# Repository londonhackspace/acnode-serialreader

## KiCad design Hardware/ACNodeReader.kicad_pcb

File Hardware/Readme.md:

ACNode Serial Reader Hardware
=============

Errata - V1.1
----
* The RX and TX lines are backwards on connector J6 - Silkscreen is as intended NOT as implemented!

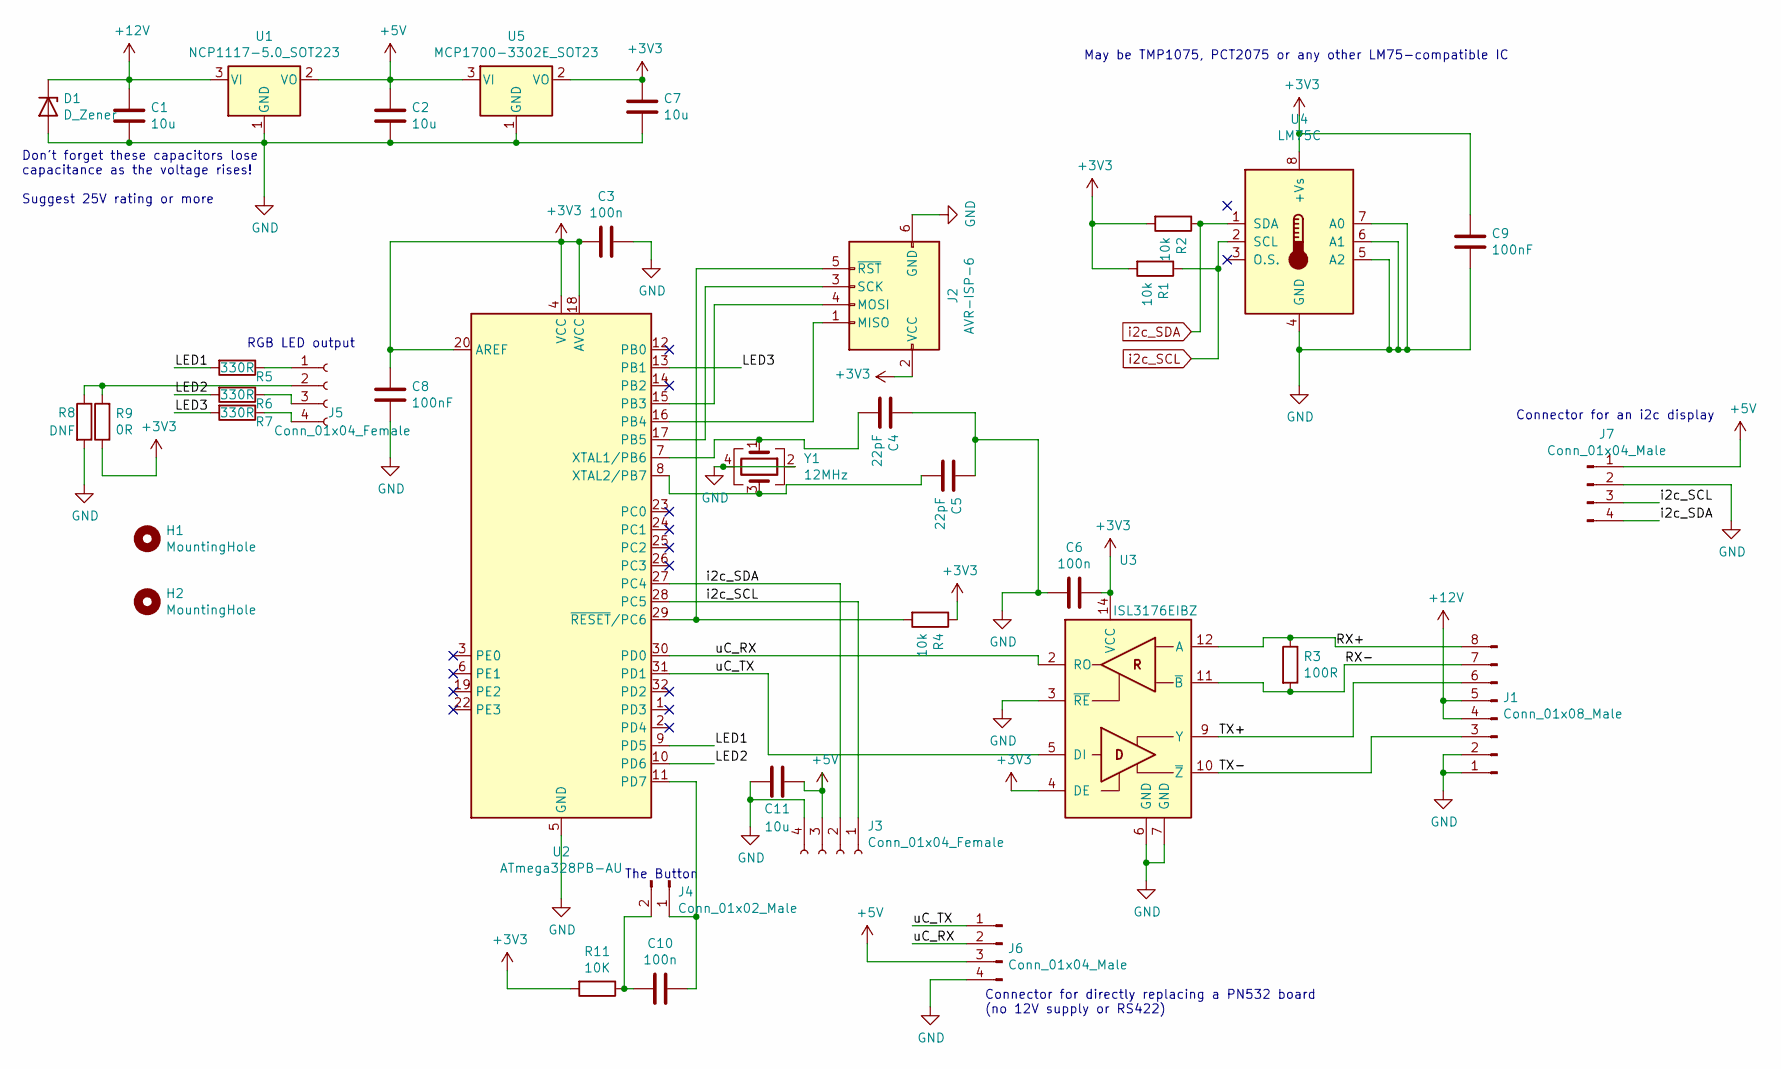
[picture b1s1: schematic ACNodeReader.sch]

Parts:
C1, C2, C7, C11: 10u; C_0805_2012Metric
C3, C6, C10: 100n; C_0603_1608Metric
C4, C5: 22pF; C_0603_1608Metric
C8, C9: 100nF; C_0603_1608Metric
D1: D_Zener; D_SOD-323F
H1, H2: MountingHole; MountingHole_3.2mm_M3_DIN965
J1: Conn_01x08_Male; PinHeader_1x08_P2.54mm_Horizontal
J2: AVR-ISP-6; TC2030-MCP-NL
J3: Conn_01x04_Female; PinHeader_1x04_P2.54mm_Vertical
J4: Conn_01x02_Male; PinHeader_1x02_P2.54mm_Horizontal
J5: Conn_01x04_Female; PinHeader_1x04_P2.54mm_Horizontal
J6: Conn_01x04_Male; PinHeader_1x04_P2.54mm_Horizontal
J7: Conn_01x04_Male; PinHeader_1x04_P2.54mm_Vertical
R1, R2, R4: 10k; R_0603_1608Metric
R3: 100R; R_0603_1608Metric
R5, R6, R7: 330R; R_0603_1608Metric
R8: DNF; R_0603_1608Metric
R9: 0R; R_0603_1608Metric
R11: 10K; R_0603_1608Metric
U1: NCP1117-5.0_SOT223; SOT-223-3_TabPin2
U2: ATmega328PB-AU; TQFP-32_7x7mm_P0.8mm
U3: ISL3176EIBZ; SOIC-14_3.9x8.7mm_P1.27mm
U4: LM75C; SO-8_3.9x4.9mm_P1.27mm
U5: MCP1700-3302E_SOT23; SOT-23
Y1: 12MHz; Crystal_SMD_7050-4Pin_7.0x5.0mm

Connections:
+3V3: C3.2, C6.1, C7.1, C8.1, C9.1, J2.2 (VCC), R1.2, R2.2, R4.1, R9.1, R11.2, U2.4 (VCC), U2.18 (AVCC), U2.20 (AREF), U3.4 (DE), U3.14 (VCC), U4.8 (+Vs), U5.2 (VO)
+5V: C2.1, C11.1, J3.3, J6.3, J7.1, U1.2 (VO), U5.3 (VI)
+12V: C1.1, D1.1 (K), J1.4, J1.5, U1.3 (VI)
/LED1: R5.2, U2.9 (PD5)
/LED2: R6.2, U2.10 (PD6)
/LED3: R7.2, U2.13 (PB1)
/RX+: J1.8, R3.1, U3.12 (A)
/RX-: J1.7, R3.2, U3.11 (~B)
/TX+: J1.6, U3.9 (Y)
/TX-: J1.3, U3.10 (~Z~)
/uC_RX: J6.2, U2.30 (PD0), U3.2 (RO)
/uC_TX: J6.1, U2.31 (PD1), U3.5 (DI)
GND: C1.2, C2.2, C3.1, C4.1, C5.1, C6.2, C7.2, C8.2, C9.2, C11.2, D1.2 (A), J1.1, J1.2, J2.6 (GND), J3.4, J6.4, J7.2, R8.2, U1.1 (GND), U2.5 (GND), U2.21 (GND), U3.3 (~RE), U3.6 (GND), U3.7 (GND), U4.4 (GND), U4.5 (A2), U4.6 (A1), U4.7 (A0), U5.1 (GND), Y1.2, Y1.4
unnamed: C4.2, U2.7 (XTAL1/PB6), Y1.1
unnamed: C5.2, U2.8 (XTAL2/PB7), Y1.3
unnamed: C10.1, J4.1, U2.11 (PD7)
unnamed: C10.2, J4.2, R11.1
unnamed: J2.1 (MISO), U2.16 (PB4)
unnamed: J2.3 (SCK), U2.17 (PB5)
unnamed: J2.4 (MOSI), U2.15 (PB3)
unnamed: J2.5 (~RST), R4.2, U2.29 (~RESET~/PC6)
unnamed: J5.1, R5.1
unnamed: J5.2, R8.1, R9.2
unnamed: J5.3, R6.1
unnamed: J5.4, R7.1
i2c_SCL: J3.1, J7.3, R1.1, U2.28 (PC5), U4.2 (SCL)
i2c_SDA: J3.2, J7.4, R2.1, U2.27 (PC4), U4.1 (SDA)

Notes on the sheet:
May be TMP1075, PCT2075 or any other LM75-compatible IC
Connector for an i2c display
Connector for directly replacing a PN532 board (no 12V supply or RS422)
The Button
RGB LED output
Don't forget these capacitors lose capacitance as the voltage rises! Suggest 25V rating or more

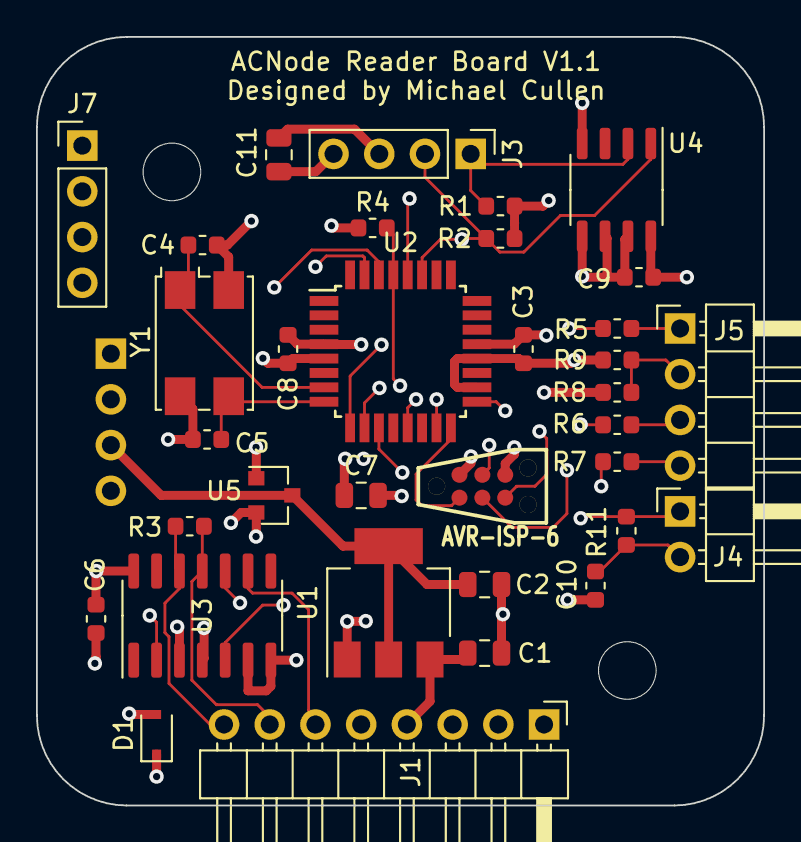
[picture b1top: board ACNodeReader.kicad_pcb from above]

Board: 4 copper layers, 40.4 x 42.7 mm, 37 parts (1 on the bottom side), 27 nets.

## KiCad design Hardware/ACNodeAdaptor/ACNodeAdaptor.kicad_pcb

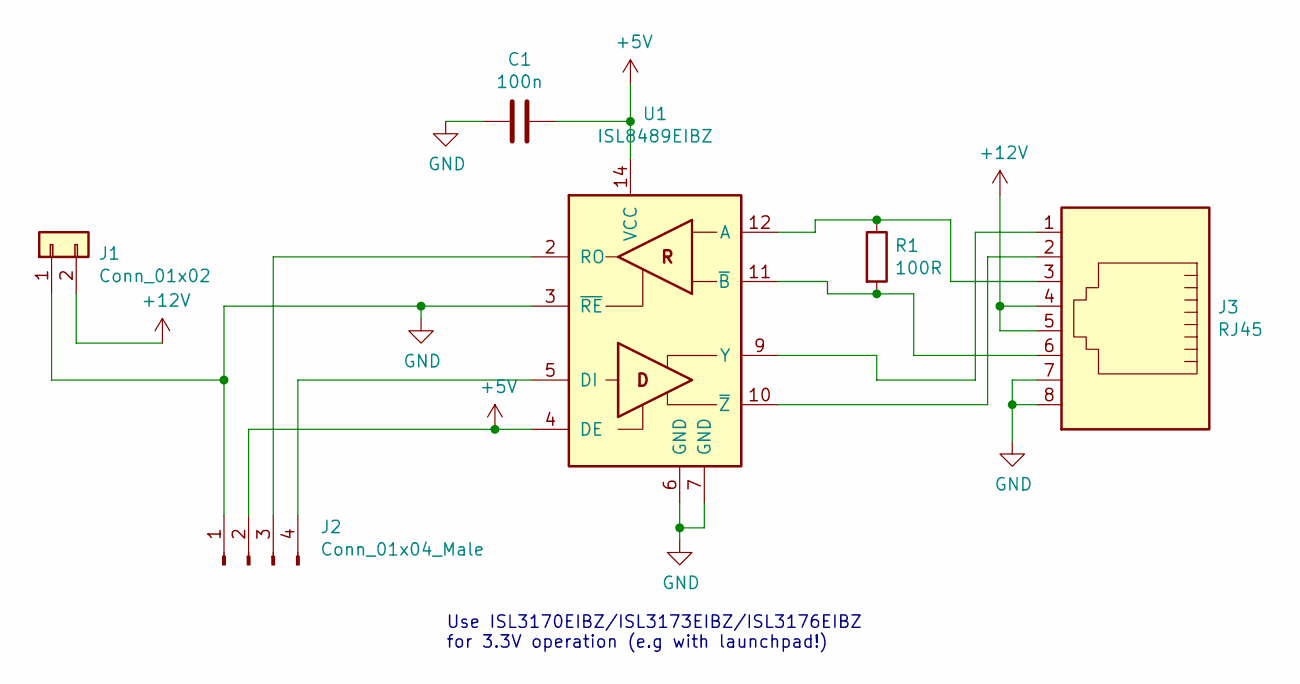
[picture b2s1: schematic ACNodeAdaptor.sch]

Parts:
C1: 100n; C_0603_1608Metric
J1: Conn_01x02; Connector-5.08mm
J2: Conn_01x04_Male; PinHeader_1x04_P2.54mm_Vertical
J3: RJ45; RJ45_Amphenol_54602-x08_Horizontal
R1: 100R; R_0603_1608Metric
U1: ISL8489EIBZ; SOIC-14_3.9x8.7mm_P1.27mm

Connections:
+5V: C1.1, J2.2, U1.4 (DE), U1.14 (VCC)
+12V: J1.2, J3.4, J3.5
GND: C1.2, J1.1, J2.1, J3.7, J3.8, U1.3 (~RE), U1.6 (GND), U1.7 (GND)
unnamed: J2.3, U1.2 (RO)
unnamed: J2.4, U1.5 (DI)
unnamed: J3.1, U1.9 (Y)
unnamed: J3.2, U1.10 (~Z~)
unnamed: J3.3, R1.1, U1.12 (A)
unnamed: J3.6, R1.2, U1.11 (~B)

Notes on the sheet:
Use ISL3170EIBZ/ISL3173EIBZ/ISL3176EIBZ for 3.3V operation (e.g with launchpad!)

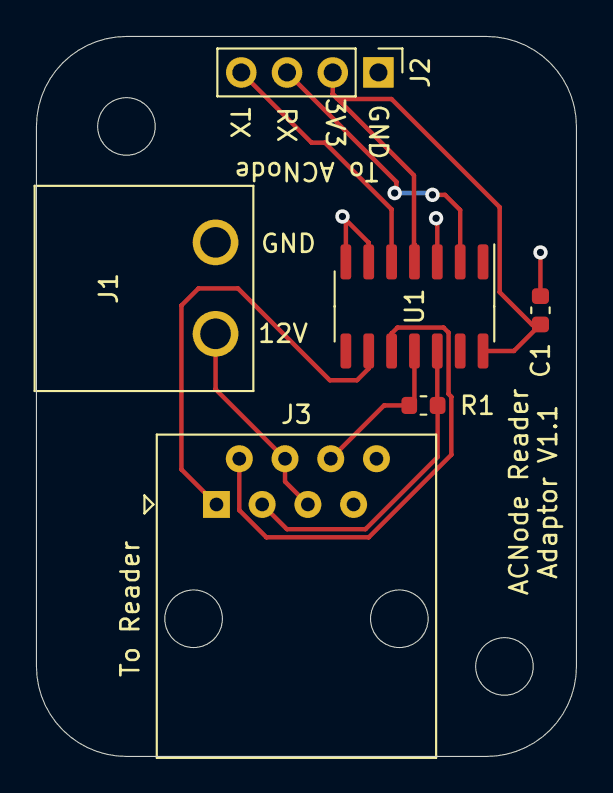
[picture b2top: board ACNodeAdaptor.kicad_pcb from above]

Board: 2 copper layers, 30.0 x 40.0 mm, 6 parts (0 on the bottom side), 9 nets.

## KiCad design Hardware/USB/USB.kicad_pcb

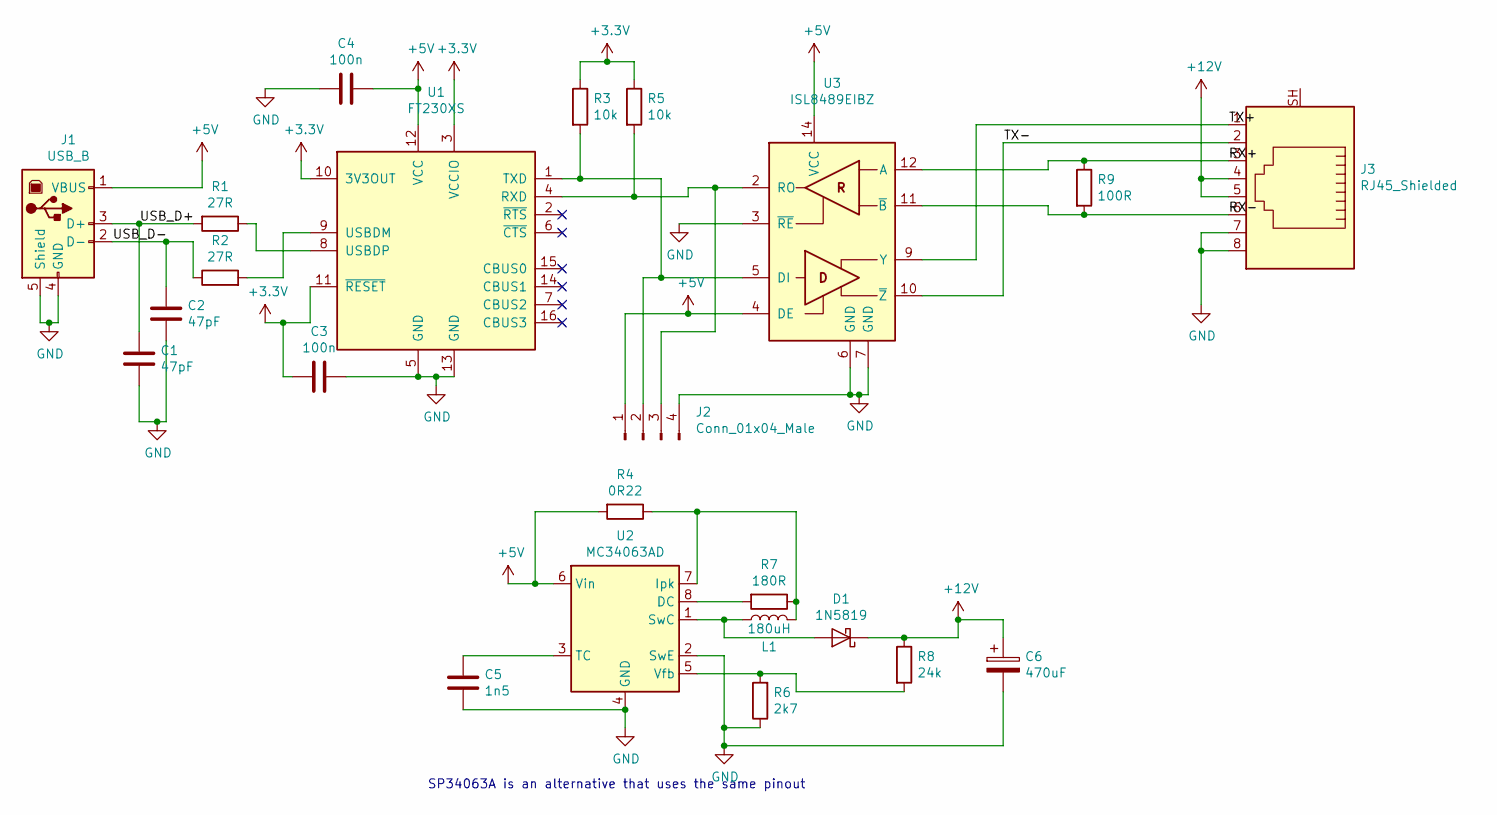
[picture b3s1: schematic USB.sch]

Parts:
C1, C2: 47pF; C_0603_1608Metric
C3, C4: 100n; C_0603_1608Metric
C5: 1n5; C_0603_1608Metric
C6: 470uF; CP_Elec_8x10
D1: 1N5819; D_DO-41_SOD81_P10.16mm_Horizontal
J1: USB_B; USB_B_OST_USB-B1HSxx_Horizontal
J2: Conn_01x04_Male; PinHeader_1x04_P2.54mm_Vertical
J3: RJ45_Shielded; RJ45_Amphenol_54602-x08_Horizontal
L1: 180uH; L_12x12mm_H8mm
R1, R2: 27R; R_0603_1608Metric
R3, R5: 10k; R_0603_1608Metric
R4: 0R22; R_0603_1608Metric
R6: 2k7; R_0603_1608Metric
R7: 180R; R_0603_1608Metric
R8: 24k; R_0603_1608Metric
R9: 100R; R_0603_1608Metric
U1: FT230XS; SSOP-16_3.9x4.9mm_P0.635mm
U2: MC34063AD; SOIC-8_3.9x4.9mm_P1.27mm
U3: ISL8489EIBZ; SOIC-14_3.9x8.7mm_P1.27mm

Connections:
+3V3: C3.2, R3.1, R5.1, U1.3 (VCCIO), U1.10 (3V3OUT), U1.11 (~RESET)
+5V: C4.1, J1.1 (VBUS), J2.1, R4.2, U1.12 (VCC), U2.6 (Vin), U3.4 (DE), U3.14 (VCC)
+12V: C6.1, D1.1 (K), J3.4, J3.5, R8.1
/RX+: J3.3, R9.1, U3.12 (A)
/RX-: J3.6, R9.2, U3.11 (~B)
/TX+: J3.1, U3.9 (Y)
/TX-: J3.2, U3.10 (~Z~)
/USB_D+: C1.1, J1.3 (D+), R1.2
/USB_D-: C2.1, J1.2 (D-), R2.1
GND: C1.2, C2.2, C3.1, C4.2, C5.2, C6.2, J1.4 (GND), J1.5 (Shield), J2.4, J3.7, J3.8, R6.1, U1.5 (GND), U1.13 (GND), U2.2 (SwE), U2.4 (GND), U3.3 (~RE), U3.6 (GND), U3.7 (GND)
unnamed: C5.1, U2.3 (TC)
unnamed: D1.2 (A), L1.1, U2.1 (SwC)
unnamed: J2.2, R3.2, U1.1 (TXD), U3.5 (DI)
unnamed: J2.3, R5.2, U1.4 (RXD), U3.2 (RO)
unnamed: L1.2, R4.1, R7.1, U2.7 (Ipk)
unnamed: R1.1, U1.8 (USBDP)
unnamed: R2.2, U1.9 (USBDM)
unnamed: R6.2, R8.2, U2.5 (Vfb)
unnamed: R7.2, U2.8 (DC)

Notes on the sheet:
SP34063A is an alternative that uses the same pinout

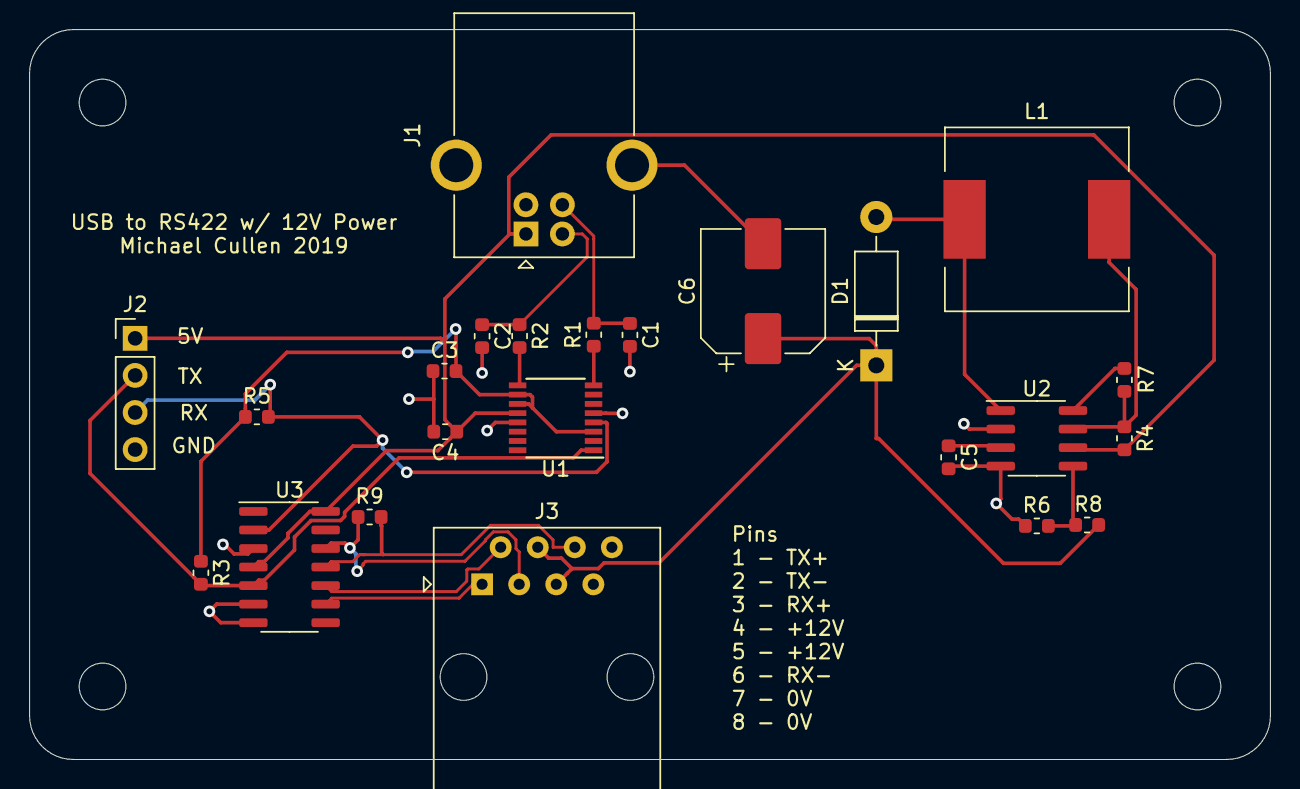
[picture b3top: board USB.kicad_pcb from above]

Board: 2 copper layers, 85.0 x 50.0 mm, 23 parts (0 on the bottom side), 19 nets.

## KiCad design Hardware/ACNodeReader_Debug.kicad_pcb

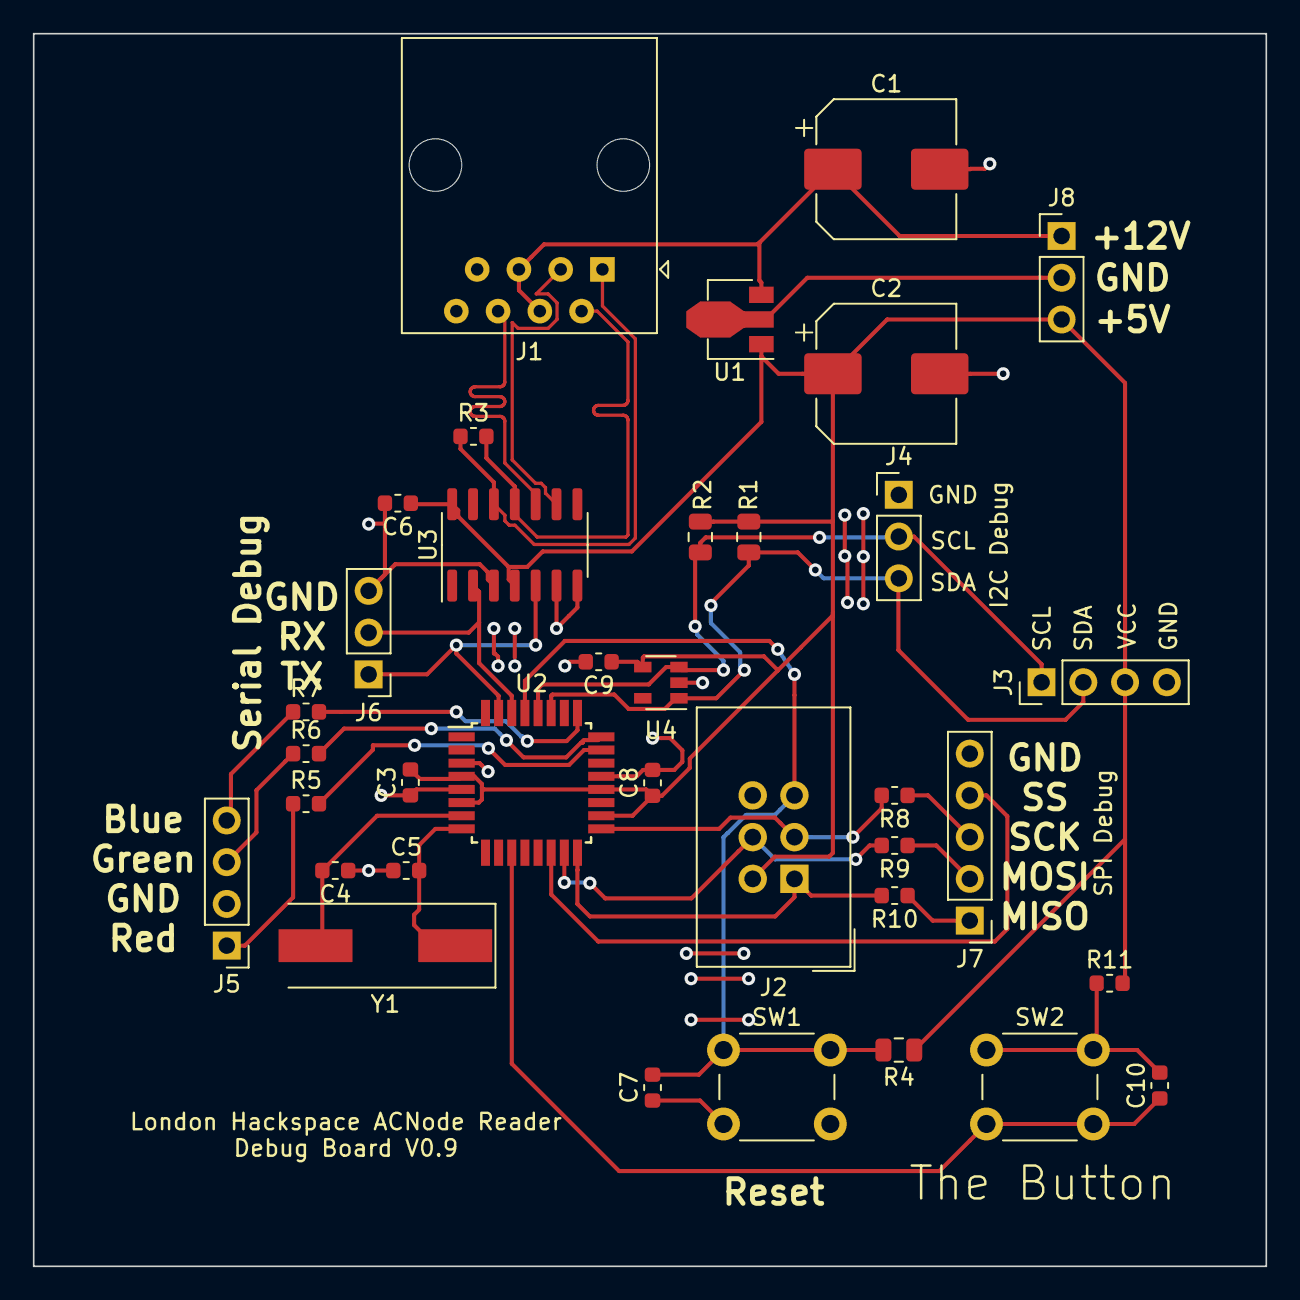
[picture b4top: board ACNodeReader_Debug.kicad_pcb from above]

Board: 2 copper layers, 75.0 x 75.0 mm, 36 parts (0 on the bottom side), 29 nets.

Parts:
C1, C2: 470u; CP_Elec_8x10
C3, C6, C10: 100n; C_0603_1608Metric
C4, C5: 22pF; C_0603_1608Metric
C7: 4.7nF; C_0603_1608Metric
C8, C9: 100nF; C_0603_1608Metric
J1: 8P8C; RJ45_Amphenol_54602-x08_Horizontal
J2: AVR-ISP-6; IDC-Header_2x03_P2.54mm_Vertical
J3, J5: Conn_01x04_Female; PinHeader_1x04_P2.54mm_Vertical
J4, J6, J8: Conn_01x03_Male; PinHeader_1x03_P2.54mm_Vertical
J7: Conn_01x05_Male; PinHeader_1x05_P2.54mm_Vertical
R1, R2, R4: 10k; R_0805_2012Metric
R3: 100R; R_0603_1608Metric
R5, R6, R7: 1K; R_0603_1608Metric
R8, R9, R10: 220R; R_0603_1608Metric
R11: R; R_0603_1608Metric
SW1, SW2: SW_Push; SW_PUSH_6mm
U1: L78L05_SOT89; SOT-89-3
U2: ATmega88-20AU; TQFP-32_7x7mm_P0.8mm
U3: ISL8489EIBZ; SOIC-14_3.9x8.7mm_P1.27mm
U4: SI7060-B-00-IV; SOT-23-5
Y1: 16MHz; Crystal_SMD_HC49-SD

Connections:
+5V: C2.1, C3.2, C6.1, C8.1, C9.1, J2.2, J3.3, J8.3, R1.2, R2.2, R4.1, R11.2, U1.1, U2.4, U2.6, U2.18, U2.20, U3.4, U3.14, U4.4
+12V: C1.1, J1.4, J1.5, J8.1, U1.3
/RX+: J1.1, R3.1, U3.12
/RX-: J1.2, R3.2, U3.11
/TX+: J1.3, U3.9
/TX-: J1.6, U3.10
GND: C1.2, C2.2, C3.1, C4.1, C5.1, C6.2, C7.1, C8.2, C9.2, J1.7, J1.8, J2.6, J3.4, J4.1, J5.2, J6.3, J7.5, J8.2, SW1.2, U1.2, U2.3, U2.5, U2.21, U3.3, U3.6, U3.7, U4.2
unnamed: C4.2, U2.7, Y1.2
unnamed: C5.2, U2.8, Y1.1
unnamed: C7.2, J2.5, R4.2, SW1.1, U2.29
unnamed: C10.1, SW2.2, U2.11
unnamed: C10.2, R11.1, SW2.1
unnamed: J2.1, R10.2, U2.16
unnamed: J2.3, R8.2, U2.17
unnamed: J2.4, R9.2, U2.15
unnamed: J5.1, R5.1
unnamed: J5.3, R6.1
unnamed: J5.4, R7.1
unnamed: J7.1, R10.1
unnamed: J7.2, R9.1
unnamed: J7.3, R8.1
unnamed: J7.4, U2.14
unnamed: R5.2, U2.23
unnamed: R6.2, U2.24
unnamed: R7.2, U2.25
i2c_SCL: J3.1, J4.2, R2.1, U2.28, U4.3
i2c_SDA: J3.2, J4.3, R1.1, U2.27, U4.1
uC_RX: J6.2, U2.30, U3.2
uC_TX: J6.1, U2.31, U3.5

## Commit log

2019-07-28 initial skeleton
2019-07-30 Added lights control functions
2019-08-02 Make dependencies work correctly
    This uses the MMD flag on GCC to make sure the dependencies are tracked
    including header files
2019-08-04 WIP: Progress so far
2019-08-04 Add Travis build file
2019-08-06 Mostly non-working PN532 code
2019-08-08 Added debug hardware
    The aim of this board is to prove the ideas. It has extra
    pins broken out for debugging and testing.
2019-08-09 Added gerbers
2019-08-18 Update a component value
2019-08-18 Firmware: Add support for new debug board
2019-08-18 Firmware: lower i2c bitrate
    Initially the code was using 400KHz I2C however that's rather high.
    It is a valid bitrate of I2C for the devices involved, but being so high,
    it's likely to be less reliable - so lower to 100KHz at least until we
    get things working properly
2019-08-18 Firmware: tidied up docs, added DebugBoard09 to build
2019-08-18 Firmware: Added missing header file
2019-08-18 Firmware: Got basic card reading working!
    This version is a bit rough and ready, but it does work. The basic idea is that it
    reads the card, and lights up green for a Mifare-ish card, or blue for a FeliCa card
    (e.g Octopus)
    The intention is to rewrite this to be more state driven, to make it easier to handle.
2019-08-18 Firmware: Add some error checking to headers
2019-08-18 Added (simple) temperature sensor support
    This commit adds support for the SI7060 I2C temperature sensor on supported boards.
2019-09-19 USB to Reader Board Board
2020-05-25 Random locl changes
2020-06-07 First pass at comms protocol and some testing of it
2020-06-09 Toying with the circuit a bit
    Removed the capacitor across reset since it breaks DebugWire which
    is worth having usable because it helps when all hell breaks loose :-)
    Added zero ohm links for switching LED from common anode to common cathode
    Switched capacitors to (much smaller) MLCC variants in preparation for attempting
    to cram everything into a smaller board
2020-08-28 New, smaller, better PCB design
2020-08-28 Slight schematic changes - mostly text descriptions
2020-08-29 Added note about reversed pinout
2020-08-29 Added adaptor board
2020-08-30 Note about 3.3V operation (e.g with a launchpad)
2020-09-19 Added some notes to schematic and updated firmware with new board support
    getting there!
2020-09-20 Lights: Add support for PWM LEDs on Rev1 board
    We now have dimmable LEDs on the Rev1 board, so no more on/off control!
2020-09-20 Add Rev1 board (Atmega88PB based)
2020-09-20 Reliability fixes
    Still needs some work, but it's looking better than it was
2020-09-20 Add LM75 support
    Basic support for getting temperatures from LM75 and similar sensors
2020-09-22 Hardware V1.1 - 3.3V with chunkier 5V regulator
    The 1.0 5V regulator wasn't chunky enough, so this board has a larger
    one to support the current draw of the PN532 module. Additionally, a
    capacitor has been added near to the PN532 module connector to assist in
    smoothing the supply to it.
    Most of the board now runs at 3.3V, derived from the 5V rail. This is to
    support direct connection to an ACNode, which only support 3.3V IO. This
2020-09-22 ACNodeAdaptor: Minor change to silkscreen
    The ACNode adaptor is actually assembled with a 3.3V RS422 driver, to
    support connection to the ACNode. This board modifies the silkscreen to
    reflect this.
2020-09-22 Remove old Arduino target
    It isn't much use now, probably doesn't work, and isn't worth maintaining
2020-09-22 Add mostly empty, useless bootloader
    Basic bootloader, not much use yet
2020-09-23 Comms and Serial Bug Fixes
    Better handling of junk in the buffer and removed a probable buffer
    overflow
2020-10-10 Makefile Tweaks
    Make REV1 default instead of non-existent Arduino target and a few other
    minor tweaks
2020-10-10 Add temperature command
    Adds the ability to query the temperature from the reader
2020-10-10 Add Rev1.1 board support to firmware
    This board runs at 12MHz to be in spec for 3.3V operation of the
    microcontroller
2020-10-10 Make Rev1.1 default in firmware build
    This is the board most likely to be used now so it makes sense for it to
    be the default target
2020-10-10 Update notes on versions
2020-10-10 Make Bootloader fit in 2Kb
    The bootloader was getting too big, so:
    1) make a bootloader mode to remove code not used
    2) remove flow control since it wasn't really much use anyway since we
    wait for responses before sending anything with this protocol
    3) Switch to -Os to make things smaller
2020-10-10 More tweaks to try to slim things down
2020-10-10 Added missing target makefile
2020-10-10 Shrink the bootloader a bit more
    we need enough space for actual code handling!
2020-10-10 Make 328 bootloader section larger
    This comms protocol is quite complicated to implement, and we were running out of bootloader space.
    This probably does mean the 88 version cannot use a bootloader, at least with this protocol.
2020-10-10 Updated hardware with how I actually assembled it
    I'm leaning towards the ATmega328PB, and also switched to 330R resistors on the LEDs
2020-11-24 More bootloader stuff
    This may have broken debug logging builds, more testing needed
2020-11-25 Basic SSD1306 display support
    VERY basic support for handling a 128x64 OLED display module
2020-11-25 Add hardware errata notes
2020-12-18 More firmware changes - Next step is probably to get the ACNode to talk to it!
2020-12-18 Update schematic PDF
2021-03-22 Fix bug in comms protocol
2021-03-24 Bugs? What Bugs?
2021-03-25 Attempt to fix travis build's missing targets
2021-03-25 MOAR STUFF
    Added some messages, the fonts that were missing from the previous commits,
    and a few other bits
2021-03-27 Some comms fixes from fuzzing
    I ran AFL over the parser and found a few crashes and hangs. This fixes some of them.
    One nasty one will need a bit more work, so that will have to wait for the next commit
2021-03-29 Add fuzz harness
    This allows stress testing the protocol parser using AFL. It does not
    attempt to parse any message payloads, however it does very effectively
    find problems in the framing and checksum stage.
2021-03-29 Fix a bug in a test
    Half a byte was somehow missing in some test data
2021-03-29 Some fixes to the comms protocol.
    It's better, but I think some parts of this need a rethink. It's still getting
    stuck a bit too often, and the way the retry parsing works feels a bit rough
